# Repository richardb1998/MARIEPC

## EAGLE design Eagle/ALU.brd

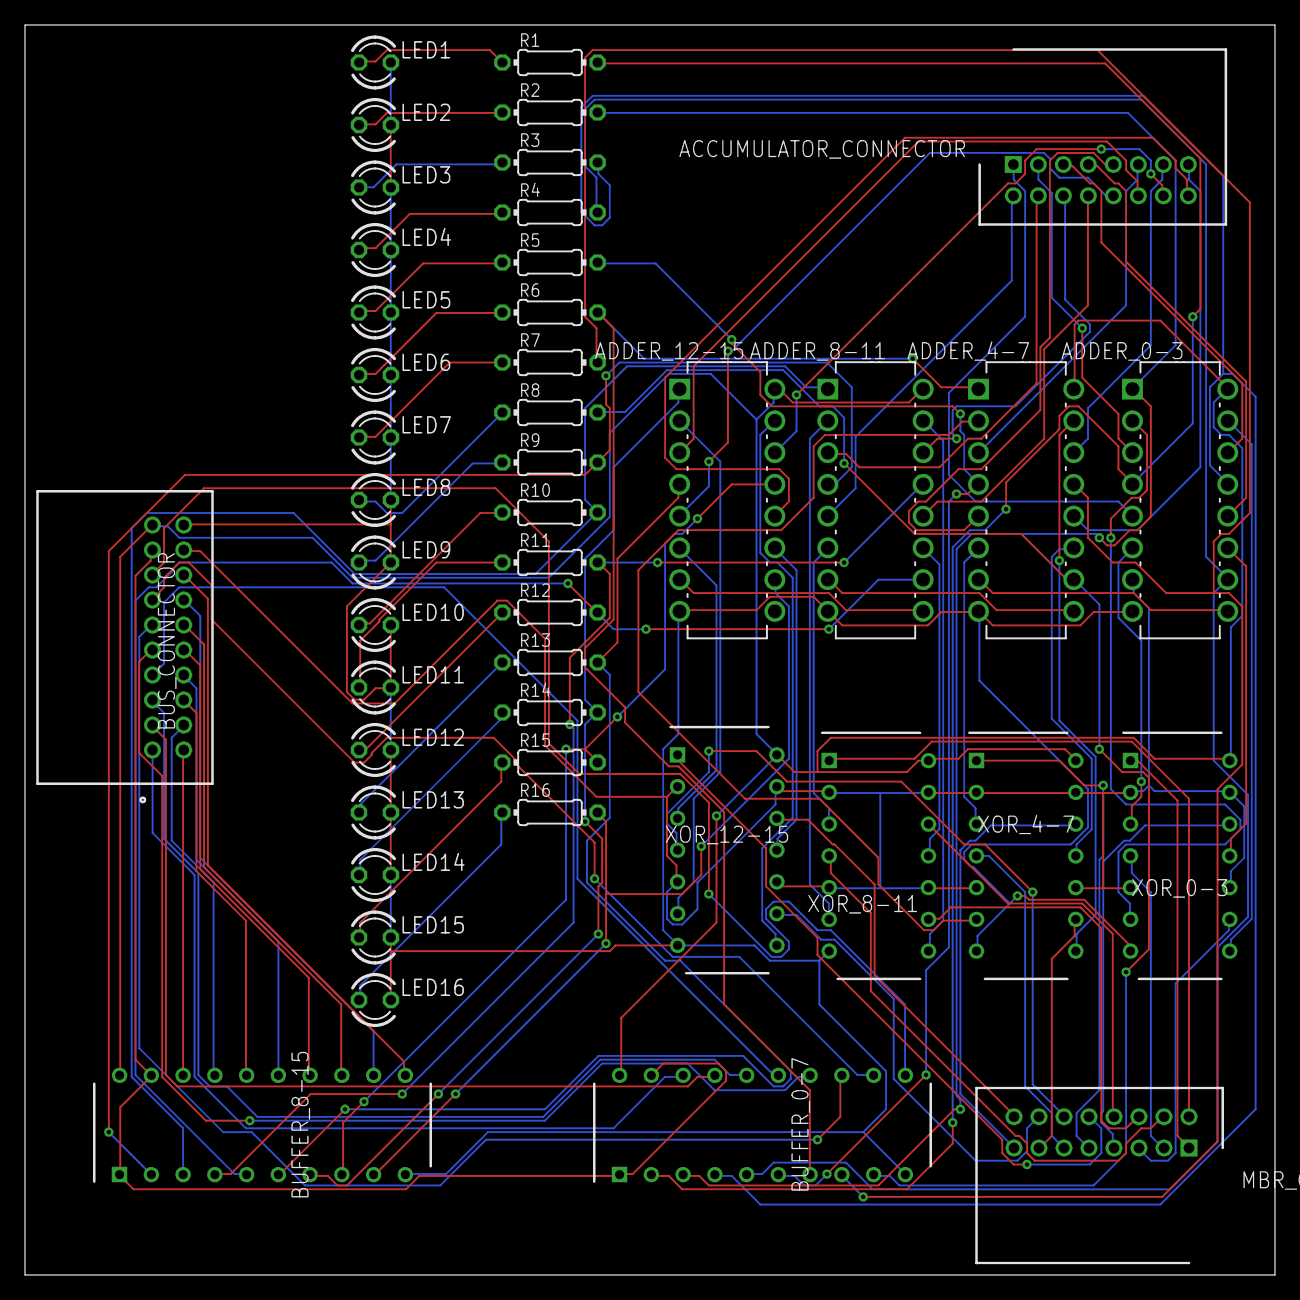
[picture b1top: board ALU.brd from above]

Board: 2 copper layers, 100.0 x 100.0 mm, 45 parts (0 on the bottom side), 103 nets.

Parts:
ACCUMULATOR_CONNECTOR: 55959-1630; SHDR16W65P250X200_2X8_1940X140
ADDER_0-3, ADDER_4-7, ADDER_8-11, ADDER_12-15: SN74F283N; DIP254P762X508-16
BUFFER_0-7, BUFFER_8-15: SN74HC541N; DIP794W53P254L2540H508Q20N
BUS_CONNECTOR: 55959-2030; 55959-2030_1
LED1, LED2, LED3, LED4, LED5, LED6, LED7, LED8, LED9, LED10, LED11, LED12, LED13, LED14, LED15, LED16: RED; LED3MM
MBR_CONNECTOR: 55959-1630; SHDR16W65P250X200_2X8_1940X140
R1, R2, R3, R4, R5, R6, R7, R8, R9, R10, R11, R12, R13, R14, R15, R16: 220; 0204/7
XOR_0-3, XOR_4-7, XOR_8-11, XOR_12-15: SN74HC86N; DIP794W53P254L1930H508Q14N

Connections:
unnamed: MBR_CONNECTOR.1, XOR_0-3.1
unnamed: MBR_CONNECTOR.3, XOR_0-3.4
unnamed: MBR_CONNECTOR.5, XOR_0-3.9
unnamed: MBR_CONNECTOR.7, XOR_0-3.12
unnamed: MBR_CONNECTOR.9, XOR_4-7.1
unnamed: MBR_CONNECTOR.11, XOR_4-7.4
unnamed: MBR_CONNECTOR.13, XOR_4-7.9
unnamed: MBR_CONNECTOR.15, XOR_4-7.12
unnamed: ADDER_0-3.6, XOR_0-3.3
unnamed: ADDER_0-3.2, XOR_0-3.6
unnamed: ADDER_0-3.15, XOR_0-3.8
unnamed: ADDER_0-3.11, XOR_0-3.11
unnamed: MBR_CONNECTOR.16, XOR_12-15.12
unnamed: MBR_CONNECTOR.14, XOR_12-15.9
unnamed: MBR_CONNECTOR.12, XOR_12-15.4
unnamed: MBR_CONNECTOR.10, XOR_12-15.1
unnamed: ADDER_4-7.9, ADDER_8-11.7
unnamed: ADDER_8-11.9, ADDER_12-15.7
unnamed: ADDER_0-3.9, ADDER_4-7.7
unnamed: MBR_CONNECTOR.8, XOR_8-11.12
unnamed: MBR_CONNECTOR.6, XOR_8-11.9
unnamed: MBR_CONNECTOR.4, XOR_8-11.4
unnamed: MBR_CONNECTOR.2, XOR_8-11.1
unnamed: ADDER_4-7.6, XOR_4-7.3
unnamed: ADDER_4-7.2, XOR_4-7.6
unnamed: ADDER_4-7.15, XOR_4-7.8
unnamed: ADDER_4-7.11, XOR_4-7.11
unnamed: ACCUMULATOR_CONNECTOR.2, ADDER_8-11.5
unnamed: ADDER_8-11.2, XOR_8-11.6
unnamed: ADDER_8-11.15, XOR_8-11.8
unnamed: ADDER_8-11.11, XOR_8-11.11
unnamed: ACCUMULATOR_CONNECTOR.15, ADDER_4-7.12
unnamed: ACCUMULATOR_CONNECTOR.13, ADDER_4-7.14
unnamed: ACCUMULATOR_CONNECTOR.11, ADDER_4-7.3
unnamed: ACCUMULATOR_CONNECTOR.9, ADDER_4-7.5
unnamed: ACCUMULATOR_CONNECTOR.7, ADDER_0-3.12
unnamed: ACCUMULATOR_CONNECTOR.5, ADDER_0-3.14
unnamed: ACCUMULATOR_CONNECTOR.3, ADDER_0-3.3
unnamed: ACCUMULATOR_CONNECTOR.1, ADDER_0-3.5
unnamed: ADDER_8-11.6, XOR_8-11.3
unnamed: ACCUMULATOR_CONNECTOR.4, ADDER_8-11.3
unnamed: ACCUMULATOR_CONNECTOR.6, ADDER_8-11.14
unnamed: ACCUMULATOR_CONNECTOR.8, ADDER_8-11.12
unnamed: ACCUMULATOR_CONNECTOR.10, ADDER_12-15.5
unnamed: ACCUMULATOR_CONNECTOR.12, ADDER_12-15.3
unnamed: ACCUMULATOR_CONNECTOR.14, ADDER_12-15.14
unnamed: ACCUMULATOR_CONNECTOR.16, ADDER_12-15.12
unnamed: ADDER_12-15.2, XOR_12-15.6
unnamed: ADDER_12-15.6, XOR_12-15.3
unnamed: ADDER_12-15.15, XOR_12-15.8
unnamed: ADDER_12-15.11, XOR_12-15.11
unnamed: ADDER_0-3.8, ADDER_4-7.8, ADDER_8-11.8, ADDER_12-15.8, BUFFER_0-7.10, BUFFER_8-15.10, BUS_CONNECTOR.20, LED1.K, LED2.K, LED3.K, LED4.K, LED5.K, LED6.K, LED7.K, LED8.K, LED9.K, LED10.K, LED11.K, LED12.K, LED13.K, LED14.K, LED15.K, LED16.K, XOR_0-3.7, XOR_4-7.7, XOR_8-11.7, XOR_12-15.7
unnamed: BUFFER_0-7.18, BUS_CONNECTOR.1
unnamed: ADDER_0-3.16, ADDER_4-7.16, ADDER_8-11.16, ADDER_12-15.16, BUFFER_0-7.20, BUFFER_8-15.20, BUS_CONNECTOR.19, XOR_0-3.14, XOR_4-7.14, XOR_8-11.14, XOR_12-15.14
unnamed: BUFFER_0-7.17, BUS_CONNECTOR.3
unnamed: BUFFER_0-7.16, BUS_CONNECTOR.5
unnamed: BUFFER_0-7.15, BUS_CONNECTOR.7
unnamed: BUFFER_0-7.14, BUS_CONNECTOR.9
unnamed: BUFFER_0-7.13, BUS_CONNECTOR.11
unnamed: BUFFER_0-7.12, BUS_CONNECTOR.13
unnamed: BUFFER_0-7.11, BUS_CONNECTOR.15
unnamed: BUFFER_8-15.15, BUS_CONNECTOR.8
unnamed: BUFFER_8-15.16, BUS_CONNECTOR.6
unnamed: BUFFER_8-15.11, BUS_CONNECTOR.16
unnamed: BUFFER_8-15.12, BUS_CONNECTOR.14
unnamed: BUFFER_8-15.13, BUS_CONNECTOR.12
unnamed: BUFFER_8-15.14, BUS_CONNECTOR.10
unnamed: BUFFER_8-15.17, BUS_CONNECTOR.4
unnamed: BUFFER_8-15.18, BUS_CONNECTOR.2
unnamed: BUFFER_0-7.1, BUFFER_0-7.19, BUFFER_8-15.1, BUFFER_8-15.19, BUS_CONNECTOR.17
unnamed: ADDER_0-3.4, BUFFER_0-7.2, R1.2
unnamed: ADDER_0-3.7, BUS_CONNECTOR.18, XOR_0-3.2, XOR_0-3.5, XOR_0-3.10, XOR_0-3.13, XOR_4-7.2, XOR_4-7.5, XOR_4-7.10, XOR_4-7.13, XOR_8-11.2, XOR_8-11.5, XOR_8-11.10, XOR_8-11.13, XOR_12-15.2, XOR_12-15.5, XOR_12-15.10, XOR_12-15.13
unnamed: ADDER_0-3.1, BUFFER_0-7.3, R2.2
unnamed: ADDER_0-3.13, BUFFER_0-7.4, R3.2
unnamed: ADDER_0-3.10, BUFFER_0-7.5, R4.2
unnamed: ADDER_4-7.4, BUFFER_0-7.6, R5.2
unnamed: ADDER_4-7.1, BUFFER_0-7.7, R6.2
unnamed: ADDER_4-7.13, BUFFER_0-7.8, R7.2
unnamed: ADDER_4-7.10, BUFFER_0-7.9, R8.2
unnamed: ADDER_8-11.4, BUFFER_8-15.2, R9.2
unnamed: ADDER_8-11.1, BUFFER_8-15.3, R10.2
unnamed: ADDER_8-11.13, BUFFER_8-15.4, R11.2
unnamed: ADDER_8-11.10, BUFFER_8-15.5, R12.2
unnamed: ADDER_12-15.4, BUFFER_8-15.6, R13.2
unnamed: ADDER_12-15.1, BUFFER_8-15.7, R14.2
unnamed: ADDER_12-15.10, BUFFER_8-15.9, R16.2
unnamed: LED16.A, R16.1
unnamed: ADDER_12-15.13, BUFFER_8-15.8, R15.2
unnamed: LED15.A, R15.1
unnamed: LED14.A, R14.1
unnamed: LED13.A, R13.1
unnamed: LED12.A, R12.1
unnamed: LED11.A, R11.1
unnamed: LED10.A, R10.1
unnamed: LED9.A, R9.1
unnamed: LED8.A, R8.1
unnamed: LED7.A, R7.1
unnamed: LED6.A, R6.1
unnamed: LED5.A, R5.1
unnamed: LED4.A, R4.1
unnamed: LED3.A, R3.1
unnamed: LED2.A, R2.1
unnamed: LED1.A, R1.1

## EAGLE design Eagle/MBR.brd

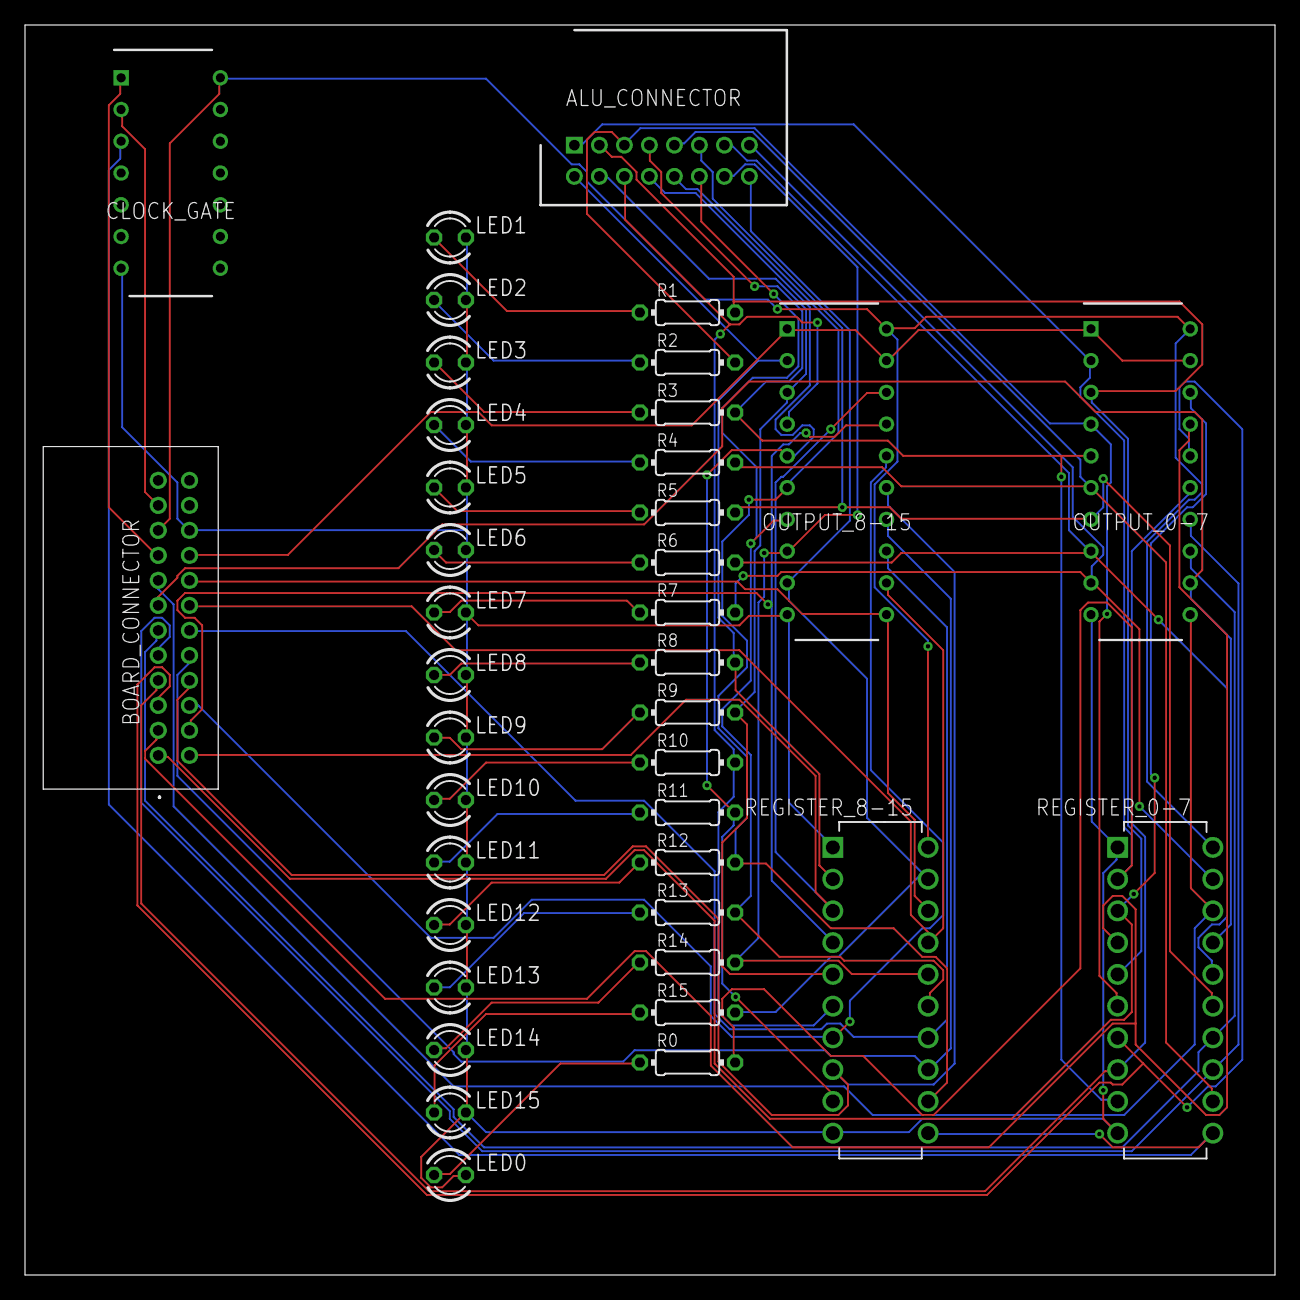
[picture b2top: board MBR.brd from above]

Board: 2 copper layers, 100.0 x 100.0 mm, 39 parts (0 on the bottom side), 54 nets.

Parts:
ALU_CONNECTOR: 55959-1630; SHDR16W65P250X200_2X8_1940X140
BOARD_CONNECTOR: 55959-2430; 559592430
CLOCK_GATE: SN74HC08N; DIP794W53P254L1930H508Q14N
LED0, LED1, LED2, LED3, LED4, LED5, LED6, LED7, LED8, LED9, LED10, LED11, LED12, LED13, LED14, LED15: RED; LED3MM
OUTPUT_0-7, OUTPUT_8-15: SN74HC541N; DIP794W53P254L2540H508Q20N
R0, R1, R2, R3, R4, R5, R6, R7, R8, R9, R10, R11, R12, R13, R14, R15: 220; 0204/7
REGISTER_0-7, REGISTER_8-15: SN74BCT374N; DIP254P762X508-20

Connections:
B8: BOARD_CONNECTOR.2, OUTPUT_8-15.18, REGISTER_8-15.3
B9: BOARD_CONNECTOR.4, OUTPUT_8-15.17, REGISTER_8-15.4
B10: BOARD_CONNECTOR.6, OUTPUT_8-15.16, REGISTER_8-15.7
B11: BOARD_CONNECTOR.8, OUTPUT_8-15.15, REGISTER_8-15.8
B12: BOARD_CONNECTOR.10, OUTPUT_8-15.14, REGISTER_8-15.13
B13: BOARD_CONNECTOR.12, OUTPUT_8-15.13, REGISTER_8-15.14
B14: BOARD_CONNECTOR.14, OUTPUT_8-15.12, REGISTER_8-15.17
B15: BOARD_CONNECTOR.16, OUTPUT_8-15.11, REGISTER_8-15.18
MBR0: ALU_CONNECTOR.1, OUTPUT_0-7.2, R0.2, REGISTER_0-7.2
MBR1: ALU_CONNECTOR.3, OUTPUT_0-7.3, R1.2, REGISTER_0-7.5
MBR2: ALU_CONNECTOR.5, OUTPUT_0-7.4, R2.2, REGISTER_0-7.6
MBR3: ALU_CONNECTOR.7, OUTPUT_0-7.5, R3.2, REGISTER_0-7.9
MBR4: ALU_CONNECTOR.9, OUTPUT_0-7.6, R4.2, REGISTER_0-7.12
MBR5: ALU_CONNECTOR.11, OUTPUT_0-7.7, R5.2, REGISTER_0-7.15
MBR6: ALU_CONNECTOR.13, OUTPUT_0-7.8, R6.2, REGISTER_0-7.16
MBR7: ALU_CONNECTOR.15, OUTPUT_0-7.9, R7.2, REGISTER_0-7.19
MBR8: ALU_CONNECTOR.2, OUTPUT_8-15.2, R8.2, REGISTER_8-15.2
MBR9: ALU_CONNECTOR.4, OUTPUT_8-15.3, R9.2, REGISTER_8-15.5
MBR10: ALU_CONNECTOR.6, OUTPUT_8-15.4, R10.2, REGISTER_8-15.6
MBR11: ALU_CONNECTOR.8, OUTPUT_8-15.5, R11.2, REGISTER_8-15.9
MBR12: ALU_CONNECTOR.10, OUTPUT_8-15.6, R12.2, REGISTER_8-15.12
MBR13: ALU_CONNECTOR.12, OUTPUT_8-15.7, R13.2, REGISTER_8-15.15
MBR14: ALU_CONNECTOR.14, OUTPUT_8-15.8, R14.2, REGISTER_8-15.16
MBR15: ALU_CONNECTOR.16, OUTPUT_8-15.9, R15.2, REGISTER_8-15.19
unnamed: BOARD_CONNECTOR.15, OUTPUT_0-7.11, REGISTER_0-7.18
unnamed: BOARD_CONNECTOR.13, OUTPUT_0-7.12, REGISTER_0-7.17
unnamed: BOARD_CONNECTOR.11, OUTPUT_0-7.13, REGISTER_0-7.14
unnamed: BOARD_CONNECTOR.9, OUTPUT_0-7.14, REGISTER_0-7.13
unnamed: BOARD_CONNECTOR.19, CLOCK_GATE.14, OUTPUT_0-7.20, OUTPUT_8-15.20, REGISTER_0-7.20, REGISTER_8-15.20
unnamed: BOARD_CONNECTOR.7, OUTPUT_0-7.15, REGISTER_0-7.8
unnamed: BOARD_CONNECTOR.5, OUTPUT_0-7.16, REGISTER_0-7.7
unnamed: BOARD_CONNECTOR.3, OUTPUT_0-7.17, REGISTER_0-7.4
unnamed: BOARD_CONNECTOR.1, OUTPUT_0-7.18, REGISTER_0-7.3
unnamed: LED0.A, R0.1
unnamed: LED1.A, R1.1
unnamed: LED2.A, R2.1
unnamed: LED3.A, R3.1
unnamed: LED4.A, R4.1
unnamed: LED5.A, R5.1
unnamed: LED6.A, R6.1
unnamed: LED7.A, R7.1
unnamed: BOARD_CONNECTOR.18, OUTPUT_0-7.1, OUTPUT_0-7.19, OUTPUT_8-15.1, OUTPUT_8-15.19
unnamed: BOARD_CONNECTOR.20, CLOCK_GATE.7, LED0.K, LED1.K, LED2.K, LED3.K, LED4.K, LED5.K, LED6.K, LED7.K, LED8.K, LED9.K, LED10.K, LED11.K, LED12.K, LED13.K, LED14.K, LED15.K, OUTPUT_0-7.10, OUTPUT_8-15.10, REGISTER_0-7.1, REGISTER_0-7.10, REGISTER_8-15.1, REGISTER_8-15.10
unnamed: CLOCK_GATE.3, REGISTER_0-7.11, REGISTER_8-15.11
unnamed: LED8.A, R8.1
unnamed: BOARD_CONNECTOR.17, CLOCK_GATE.1
unnamed: BOARD_CONNECTOR.21, CLOCK_GATE.2
unnamed: LED9.A, R9.1
unnamed: LED10.A, R10.1
unnamed: LED11.A, R11.1
unnamed: LED12.A, R12.1
unnamed: LED13.A, R13.1
unnamed: LED14.A, R14.1
unnamed: LED15.A, R15.1

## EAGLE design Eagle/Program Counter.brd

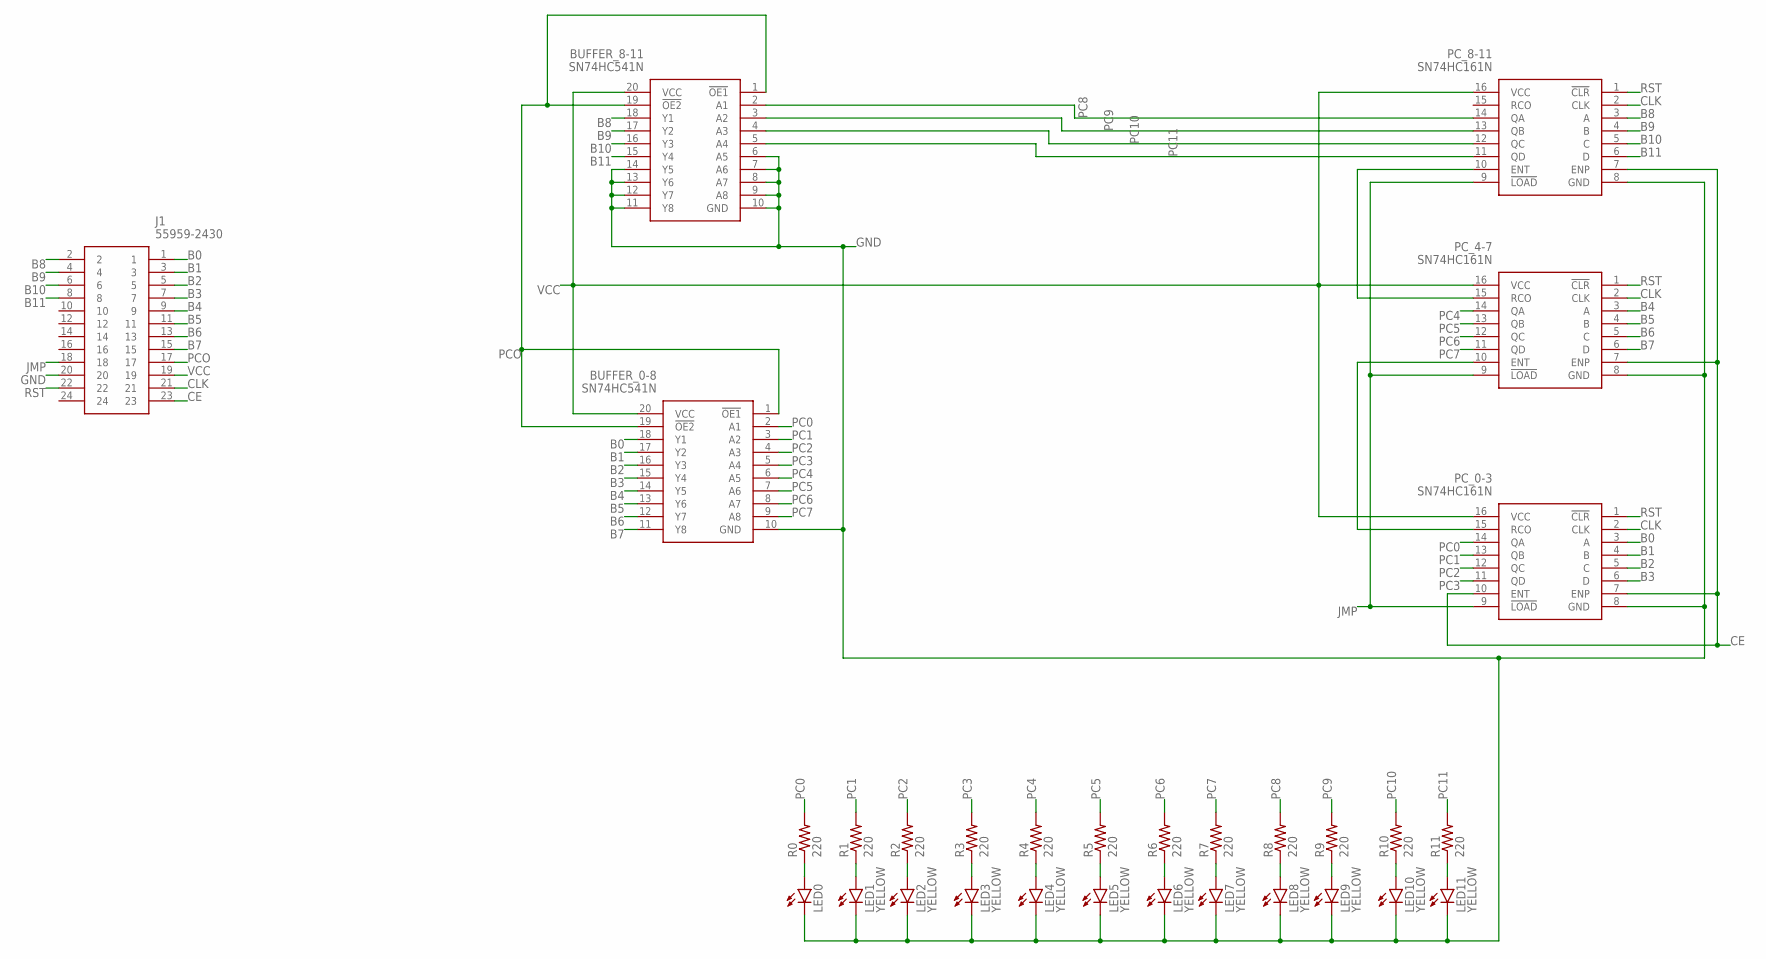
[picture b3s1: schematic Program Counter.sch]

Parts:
BUFFER_0-8, BUFFER_8-11: SN74HC541N; DIP794W53P254L2540H508Q20N
J1: 55959-2430; 559592430
LED0: LED3MM
LED1, LED2, LED3, LED4, LED5, LED6, LED7, LED8, LED9, LED10, LED11: YELLOW; LED3MM
PC_0-3, PC_4-7, PC_8-11: SN74HC161N; DIP794W53P254L1930H508Q16N
R0, R1, R2, R3, R4, R5, R6, R7, R8, R9, R10, R11: 220; 0204/7

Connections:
B0: BUFFER_0-8.18 (Y1), J1.1, PC_0-3.3 (A)
B1: BUFFER_0-8.17 (Y2), J1.3, PC_0-3.4 (B)
B2: BUFFER_0-8.16 (Y3), J1.5, PC_0-3.5 (C)
B3: BUFFER_0-8.15 (Y4), J1.7, PC_0-3.6 (D)
B4: BUFFER_0-8.14 (Y5), J1.9, PC_4-7.3 (A)
B5: BUFFER_0-8.13 (Y6), J1.11, PC_4-7.4 (B)
B6: BUFFER_0-8.12 (Y7), J1.13, PC_4-7.5 (C)
B7: BUFFER_0-8.11 (Y8), J1.15, PC_4-7.6 (D)
B8: BUFFER_8-11.18 (Y1), J1.2, PC_8-11.3 (A)
B9: BUFFER_8-11.17 (Y2), J1.4, PC_8-11.4 (B)
B10: BUFFER_8-11.16 (Y3), J1.6, PC_8-11.5 (C)
B11: BUFFER_8-11.15 (Y4), J1.8, PC_8-11.6 (D)
CE: J1.23, PC_0-3.7 (ENP), PC_0-3.10 (ENT), PC_4-7.7 (ENP), PC_8-11.7 (ENP)
CLK: J1.21, PC_0-3.2 (CLK), PC_4-7.2 (CLK), PC_8-11.2 (CLK)
GND: BUFFER_0-8.10 (GND), BUFFER_8-11.6 (A5), BUFFER_8-11.7 (A6), BUFFER_8-11.8 (A7), BUFFER_8-11.9 (A8), BUFFER_8-11.10 (GND), BUFFER_8-11.11 (Y8), BUFFER_8-11.12 (Y7), BUFFER_8-11.13 (Y6), BUFFER_8-11.14 (Y5), J1.20, LED0.K (C), LED1.K (C), LED2.K (C), LED3.K (C), LED4.K (C), LED5.K (C), LED6.K (C), LED7.K (C), LED8.K (C), LED9.K (C), LED10.K (C), LED11.K (C), PC_0-3.8 (GND), PC_4-7.8 (GND), PC_8-11.8 (GND)
JMP: J1.18, PC_0-3.9 (!LOAD), PC_4-7.9 (!LOAD), PC_8-11.9 (!LOAD)
unnamed: PC_0-3.15 (RCO), PC_4-7.10 (ENT)
unnamed: PC_4-7.15 (RCO), PC_8-11.10 (ENT)
unnamed: LED0.A, R0.1
unnamed: LED1.A, R1.1
unnamed: LED2.A, R2.1
unnamed: LED3.A, R3.1
unnamed: LED4.A, R4.1
unnamed: LED5.A, R5.1
unnamed: LED6.A, R6.1
unnamed: LED7.A, R7.1
unnamed: LED8.A, R8.1
unnamed: LED9.A, R9.1
unnamed: LED10.A, R10.1
unnamed: LED11.A, R11.1
PC0: BUFFER_0-8.2 (A1), PC_0-3.14 (QA), R0.2
PC1: BUFFER_0-8.3 (A2), PC_0-3.13 (QB), R1.2
PC2: BUFFER_0-8.4 (A3), PC_0-3.12 (QC), R2.2
PC3: BUFFER_0-8.5 (A4), PC_0-3.11 (QD), R3.2
PC4: BUFFER_0-8.6 (A5), PC_4-7.14 (QA), R4.2
PC5: BUFFER_0-8.7 (A6), PC_4-7.13 (QB), R5.2
PC6: BUFFER_0-8.8 (A7), PC_4-7.12 (QC), R6.2
PC7: BUFFER_0-8.9 (A8), PC_4-7.11 (QD), R7.2
PC8: BUFFER_8-11.2 (A1), PC_8-11.14 (QA), R8.2
PC9: BUFFER_8-11.3 (A2), PC_8-11.13 (QB), R9.2
PC10: BUFFER_8-11.4 (A3), PC_8-11.12 (QC), R10.2
PC11: BUFFER_8-11.5 (A4), PC_8-11.11 (QD), R11.2
PCO: BUFFER_0-8.1 (!OE1), BUFFER_0-8.19 (!OE2), BUFFER_8-11.1 (!OE1), BUFFER_8-11.19 (!OE2), J1.17
RST: J1.22, PC_0-3.1 (!CLR), PC_4-7.1 (!CLR), PC_8-11.1 (!CLR)
VCC: BUFFER_0-8.20 (VCC), BUFFER_8-11.20 (VCC), J1.19, PC_0-3.16 (VCC), PC_4-7.16 (VCC), PC_8-11.16 (VCC)

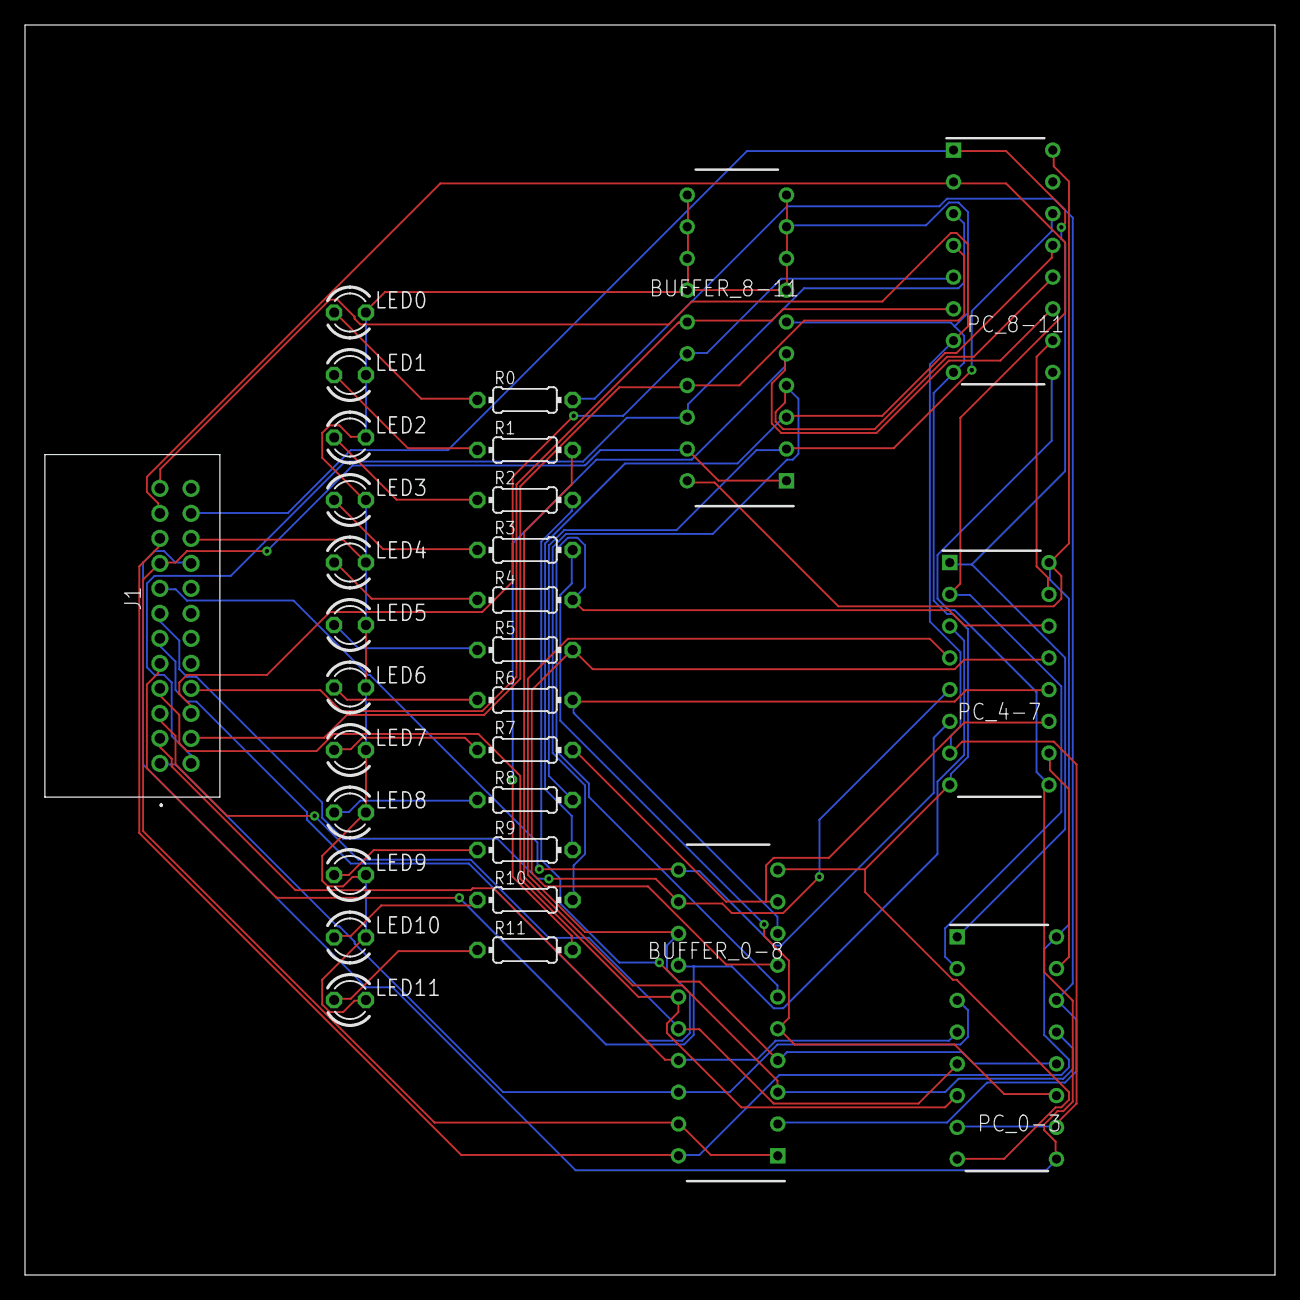
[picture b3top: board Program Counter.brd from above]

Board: 2 copper layers, 100.0 x 100.0 mm, 30 parts (0 on the bottom side), 45 nets.
